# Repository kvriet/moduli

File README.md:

# moduli
Modular light system
Published under a CC BY-NC-SA license by Katrien van Riet

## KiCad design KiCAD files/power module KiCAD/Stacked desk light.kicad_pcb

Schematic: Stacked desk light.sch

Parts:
D1: LED; LED_0805_2012Metric_Pad1.15x1.40mm_HandSolder
F1: Fuse_Small; Fuse_0805_2012Metric_Pad1.15x1.40mm_HandSolder
H1, H2: Hex_Conn_v2; Conn_hex_v2
J1: USB_B_Micro; USB_Micro-B_MC-026
R1: 150; R_0805_2012Metric_Pad1.15x1.40mm_HandSolder
SW1: SW_DIP_x01; SW_CuK_OS102011MA1QN1_SPDT_Angled

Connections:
+5V: H1.7, H2.7, R1.2, SW1.2
GND: D1.1 (K), H1.1, H1.2, H1.3, H1.4, H1.5, H1.6, H2.1, H2.2, H2.3, H2.4, H2.5, H2.6, J1.5 (GND), J1.6 (Shield)
unnamed: D1.2 (A), R1.1
unnamed: F1.1, SW1.1
unnamed: F1.2, J1.1 (VBUS)

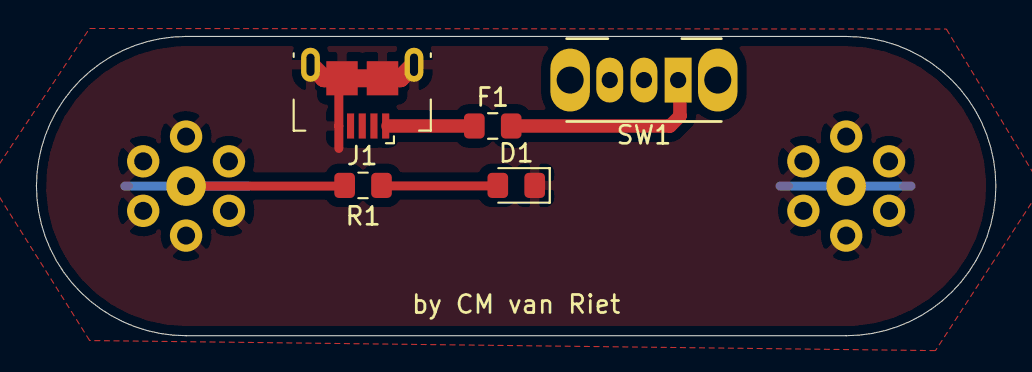
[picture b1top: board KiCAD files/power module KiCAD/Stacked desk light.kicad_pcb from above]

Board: 2 copper layers, 53.3 x 16.6 mm, 7 parts (0 on the bottom side), 5 nets.

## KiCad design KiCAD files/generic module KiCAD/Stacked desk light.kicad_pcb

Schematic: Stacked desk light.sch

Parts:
D1: LED; LED_0805_2012Metric_Pad1.15x1.40mm_HandSolder
H1, H2: Hex_Conn_v2; Conn_hex_v2
R1: 150; R_0805_2012Metric_Pad1.15x1.40mm_HandSolder

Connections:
+5V: H1.7, H2.7, R1.2
GND: D1.1 (K), H1.1, H1.2, H1.3, H1.4, H1.5, H1.6, H2.1, H2.2, H2.3, H2.4, H2.5, H2.6
unnamed: D1.2 (A), R1.1

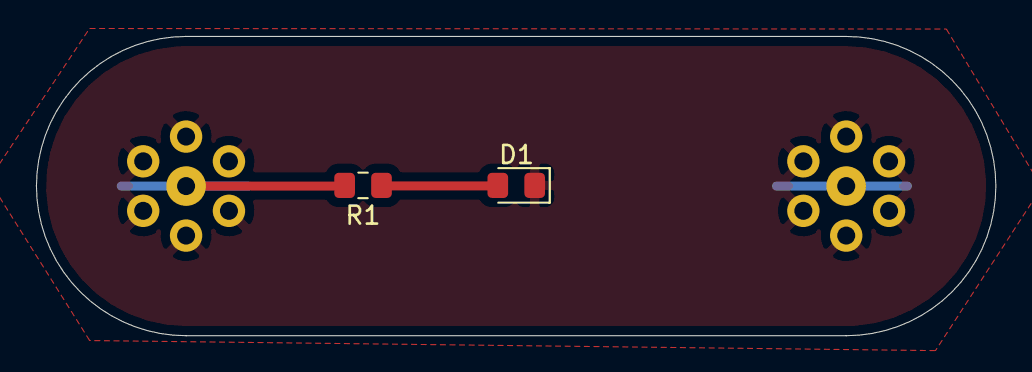
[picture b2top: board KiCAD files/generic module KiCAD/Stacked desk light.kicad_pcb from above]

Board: 2 copper layers, 53.3 x 16.6 mm, 4 parts (0 on the bottom side), 3 nets.

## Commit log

2021-03-09 Rename generic module/Stacked desk light-B_Cu.gbr to generic module gerbers/Stacked desk light-B_Cu.gbr
2021-05-02 All new versions of generic and power boards
